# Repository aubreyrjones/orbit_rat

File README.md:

Orbit Rat
---------

[Watch a demo](https://www.youtube.com/watch?v=k3nQiXu3pM4)

THIS IS NOT A MOUSE REPLACEMENT. The Orbit Rat is a Teensy LC based PC input device designed
to facilitate panning and orbiting in CAD and graphic design software.

The concept is similar to the 3dconnexion navigation device. But the Orbit Rat has fewer 
degrees of freedom, much wider compatibility, and much lower cost. The Orbit Rat is not 
quite a space mouse, you see.

The OR is designed around a pair of small joysticks, like those on a gamepad controller. These 
joysticks then control pan and orbit in CAD, art, and graphic design programs by specially
emulating a mouse. _No special drivers or plugins needed_, works in any operating system.

This is not a regular joystick-controlled mouse. OR implements a special "rewind" operation
after every motion, which resets the mouse cursor position and unlocks near-infinite pan/orbit 
in any program that uses middle-click and drag for pan.

The cost to build one is around $30 USD. You could build it without any soldering, using
breadboard, but it will be bulky. You can easily solder it on protoboard with hand wiring.
It's also an easy circuit board to design.

Tested on Linux and Windows. Should work on Mac and mobile OS as well.

Tested to work with default settings in:

* Fusion 360
* Inkscape
* GIMP
* EAGLE CAD

# How it Works

This is pretty configurable, but by default...

When you tilt the stick outside the deadzone, Orbit Rat emulates a mouse holding down the middle
mouse button and starting a drag motion. This starts a pan action in lots of CAD and art software. 
The viewport will move as if you're panning with the mouse so long as you're tiling the stick.

If you think about how your favorite software works, when you finish the pan motion and let go the button,
the mouse is in a different part of the screen than when you started. You have to 
move the cursor back toward the middle of the screen to get more space if you want to continue the pan. 
With a traditional joystick-controlled mouse, this is torture.

But not so with Orbit Rat.

As you move, the OR tracks how much mouse motion it has sent to your computer. When you let
go of the stick, it very quickly moves the cursor back to where it was when you first tilted the stick. 
You can now continue the pan just by tilting the stick again. Or, you can continue your work 
with the cursor just where you left it.

The other stick works very similarly, but also emulates holding down the left shift keyboard button. 
This will activate an orbit in CAD software.

This is almost as much control as a dedicated "3d mouse" with special driver support. The beauty of 
Orbit Rat is that it works everywhere, in any operating system, in any application that uses click 
and drag for pan.

It can also do other stuff, like sending scroll wheel events and keyboard keys... but the rewind
operation is what it does uniquely.

# Features

* User defined list of stick modes and parameters to use. As many as you like until
  you run out of RAM. Most of what's discussed below can be set per mode.

* Cycle through your defined modes by clicking the stick buttons.

* REWIND - stick initiates a mouse movement, then OR returns the cursor to its starting
  position when you let go of the stick.

* STUTTER - similar to rewind mode, but continually moves a set distance, rewinds, then 
  repeats as long as you hold down the button. Not smooth, but allows "infinite" scrolling
  with limited screen real estate.

* SIMPLE - just be a mouse cursor, no rewind.

* SCROLL - stick movement sends scroll wheel commands. Useful for CAD zoom, or
  document scrolling.

* User-defined stick curves, so you can tweak the sensitivity of each stick.

* Invert or ignore any stick axis.

* Choose mouse button(s) and/or keyboard key that is held during mouse motion.

* Auto-calibrates joysticks by default (although not perfectly)

* Configurable to send HID joystick events if desired for custom application code.

* Parts are available circa Q2 2022. Teensy LC available despite chip shortage. 
  Joysticks and other parts available from hobby electronics suppliers (Sparkfun, 
  Adafruit).

# _Planned_ Features

* RGB status LEDs (DotStar) for each stick's modes
* PCB reference design
* Left-handed PCB design

# Limitations

The Orbit Rat is fundamentally impersonating a mouse, so it doesn't have access to any
information a regular dumb mouse wouldn't have. It doesn't get any feedback from the 
operating system.

The main place this shows up is when the cursor hits the edge of the screen during a move.
The Orbit Rat thinks it's still moving the cursor, but the OS doesn't let it leave the screen.
When the OR goes to rewind the cursor motion at the end of the move, it has the wrong
idea of how much to rewind and overshoots.

Additionally, moue wheel scrolling in Linux and Windows is _not_ smooth. It goes in
chunky, discrete increments. Orbit Rat tries its best to send scroll events at a steady
rate, but without special drivers, it can't make the screen animation smooth when
scrolling (like e.g. Apple trackpad scrolling).

# Configuration and Building

Since you need the tools to upload the firmware anyway, I made things easy for me.
Orbit Rat is configured in source code and built with [PlatformIO](https://platformio.org/).

The easiest way to use PlatformIO is just to use VisualStudio Code (not Visual Studio) with
the free PlatformIO plugin from the marketplace. Standalone setups may work but I haven't
tested them.

When you first build, it may seem to stall for a very long time. PlatformIO is downloading a newer
compiler from a very slow connection. It gives no progress indicator. It seriously
took me 20 minutes to download. This only happens the first time you build. It also
may finish the download, try to compile, then say it failed... try again before
concluding it doesn't work.

Configuration is at the top of `main.cpp`. You can learn more about the options in 
`config_types.hpp`.

On your operation system you will need to set the "Teensyduino OrbitRat Mouse" acceleration
to 0. If you don't, the cursor will not return to the correct location. You should be able
to leave acceleration on for your regular mouse however you like it.

## Hardware

This isn't commercial hardware or software. You'll need to cobble together your
own hardware setup.

I'm using a Teensy LC as my microcontroller. I expect Teensy 4.0 would work, but
little is gained from its expanded capabilities. Teensy 3 might work; Teensy 2
is not compatible.

Assuming you'll use the software mostly unmodified, you need to hook up a pair of
potentiometer joysticks to the Teensy's analog inputs. That's pretty much it.

For the prototype I used the model of joystick sold on SparkFun, along with their 
breakout boards. I wired up the axes directly to the Teensy LC analog pins. I added 
pullup resistors on the switches There are internal pullups that could work, but I 
didn't test that way.

You can see my pin assignments in `main.cpp` under `axisPins` and `buttonPins`.
That's also where you can alter them if you'd like to wire the pins up differently.
Note that you _must_ use analog inputs for the joysticks.

## Software

The software isn't written to be especially efficient. It's written for a Teensy LC,
which has a 48MHz core clock. I haven't noticed that input rates are too low, so
I don't worry about a bit of fake floating point.

Calibration is quasi-automatic right now (although you can turn it off). By default, 
the center point is read at startup. Conservative endpoints are taken as a default,
but will expand if they receive a higher value from the hardware during operation. You 
can turn off both these features at the top of `main.cpp`.

## Troubleshooting

> Problem: I flashed the firmware and plugged it into the computer, but my mouse doesn't 
work or moves erratically.

This is "normal" if you flash the Teensy with Orbit Rat firmware, but have not attached
the joysticks to it. Without the joysticks, the Teensy input voltages drift randomly
and result in erratic movement. Ideally, install both joysticks. If you need just
one joystick for some reason, adjust `n_axes` to equal `2` and fix the resultant
compile errors.

## This is not a commercial venture, and the Orbit Rat is not for sale

The whole point of the project is that it's very, very cheap compared to the pro-grade
alternative. Stocking the parts, assembling them, and shipping them takes time
I have no interest in spending. And people have expectations of commercial products
(warranties, returns, etc.) that I don't want to deal with. I have a job, and a
few bucks just isn't worth the hassle.

To make it worth it to me, each unit would need to sell for $100 or more. And
that kind of defeats the purpose.

On the other hand, this is also an absolutely _ideal_ first microcontroller project.
You can build a completely decent version using just breakout- and bread-boards.
It is within your abilities to Orbit Rat. I believe in you.

You can also try one of the circuit boards from the `circuits` directory.
Most of those designs aren't tested, but they're a good starting point for
your design. When I get a design printed and tested, I will mark it 
conspicuously.

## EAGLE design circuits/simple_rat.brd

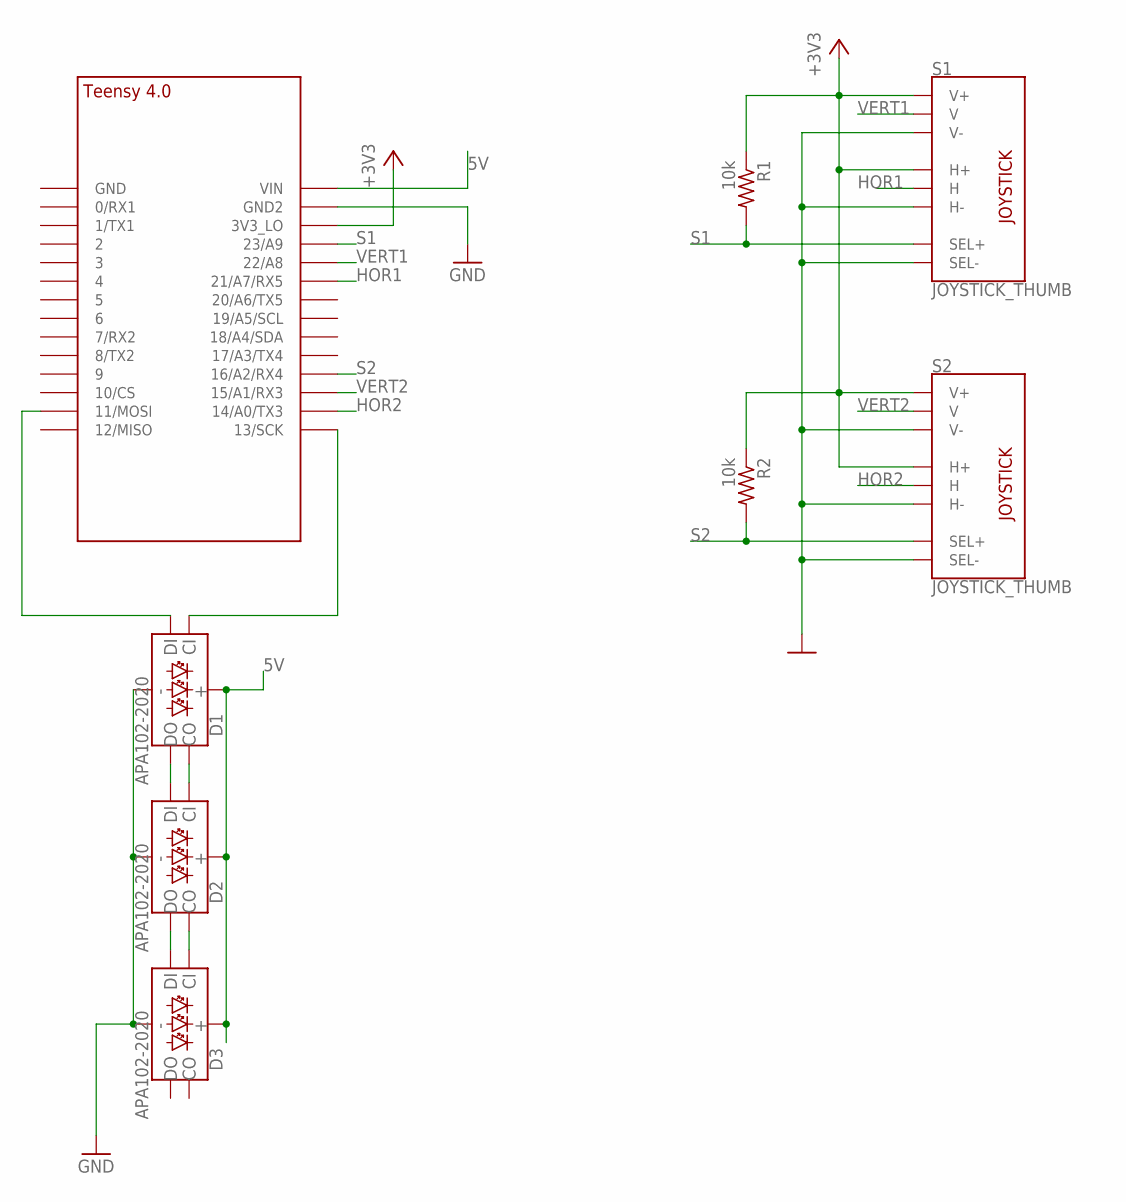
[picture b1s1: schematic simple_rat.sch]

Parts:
D1, D2, D3: APA102-2020
MCU: TEENSY_4.0-NOBOTTOM
R1, R2: 10k; R0603
S1, S2: JOYSTICK_THUMB; JOYSTICK

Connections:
5V: D1.5V_VIA (VCC), D1.VDD (VCC), D2.5V_VIA (VCC), D2.VDD (VCC), D3.5V_VIA (VCC), D3.VDD (VCC), MCU.VIN
+3V3: MCU.3V3_LO, R1.1, R2.1, S1.H1 (H+), S1.V1 (V+), S2.H1 (H+), S2.V1 (V+)
GND: D1.GND, D1.GND_VIA (GND), D2.GND, D2.GND_VIA (GND), D3.GND, D3.GND_VIA (GND), MCU.GND2, S1.B2A (SEL-), S1.H3 (H-), S1.V3 (V-), S2.B2A (SEL-), S2.H3 (H-), S2.V3 (V-)
HOR1: MCU.21/A7 (21/A7/RX5), S1.H2 (H)
HOR2: MCU.14/A0 (14/A0/TX3), S2.H2 (H)
unnamed: D1.SDO (DO), D2.SDI (DI)
unnamed: D1.CKO (CO), D2.CKI (CI)
unnamed: D2.SDO (DO), D3.SDI (DI)
unnamed: D2.CKO (CO), D3.CKI (CI)
unnamed: D1.CKI (CI), MCU.13/SCK
unnamed: D1.SDI (DI), MCU.11/MOSI
S1: MCU.23/A9, R1.2, S1.B1A (SEL+)
S2: MCU.16/A2 (16/A2/RX4), R2.2, S2.B1A (SEL+)
VERT1: MCU.22/A8, S1.V2 (V)
VERT2: MCU.15/A1 (15/A1/RX3), S2.V2 (V)

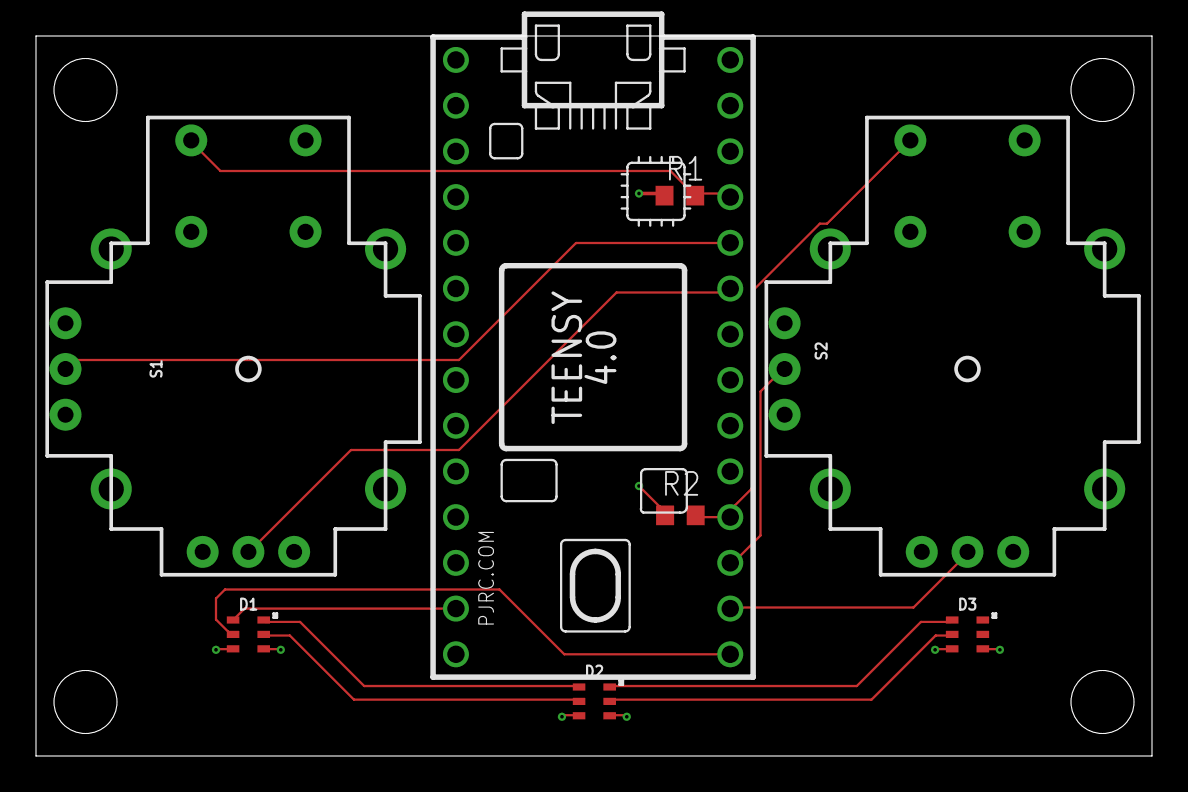
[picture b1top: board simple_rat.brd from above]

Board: 4 copper layers, 62.0 x 40.0 mm, 8 parts (0 on the bottom side), 15 nets.

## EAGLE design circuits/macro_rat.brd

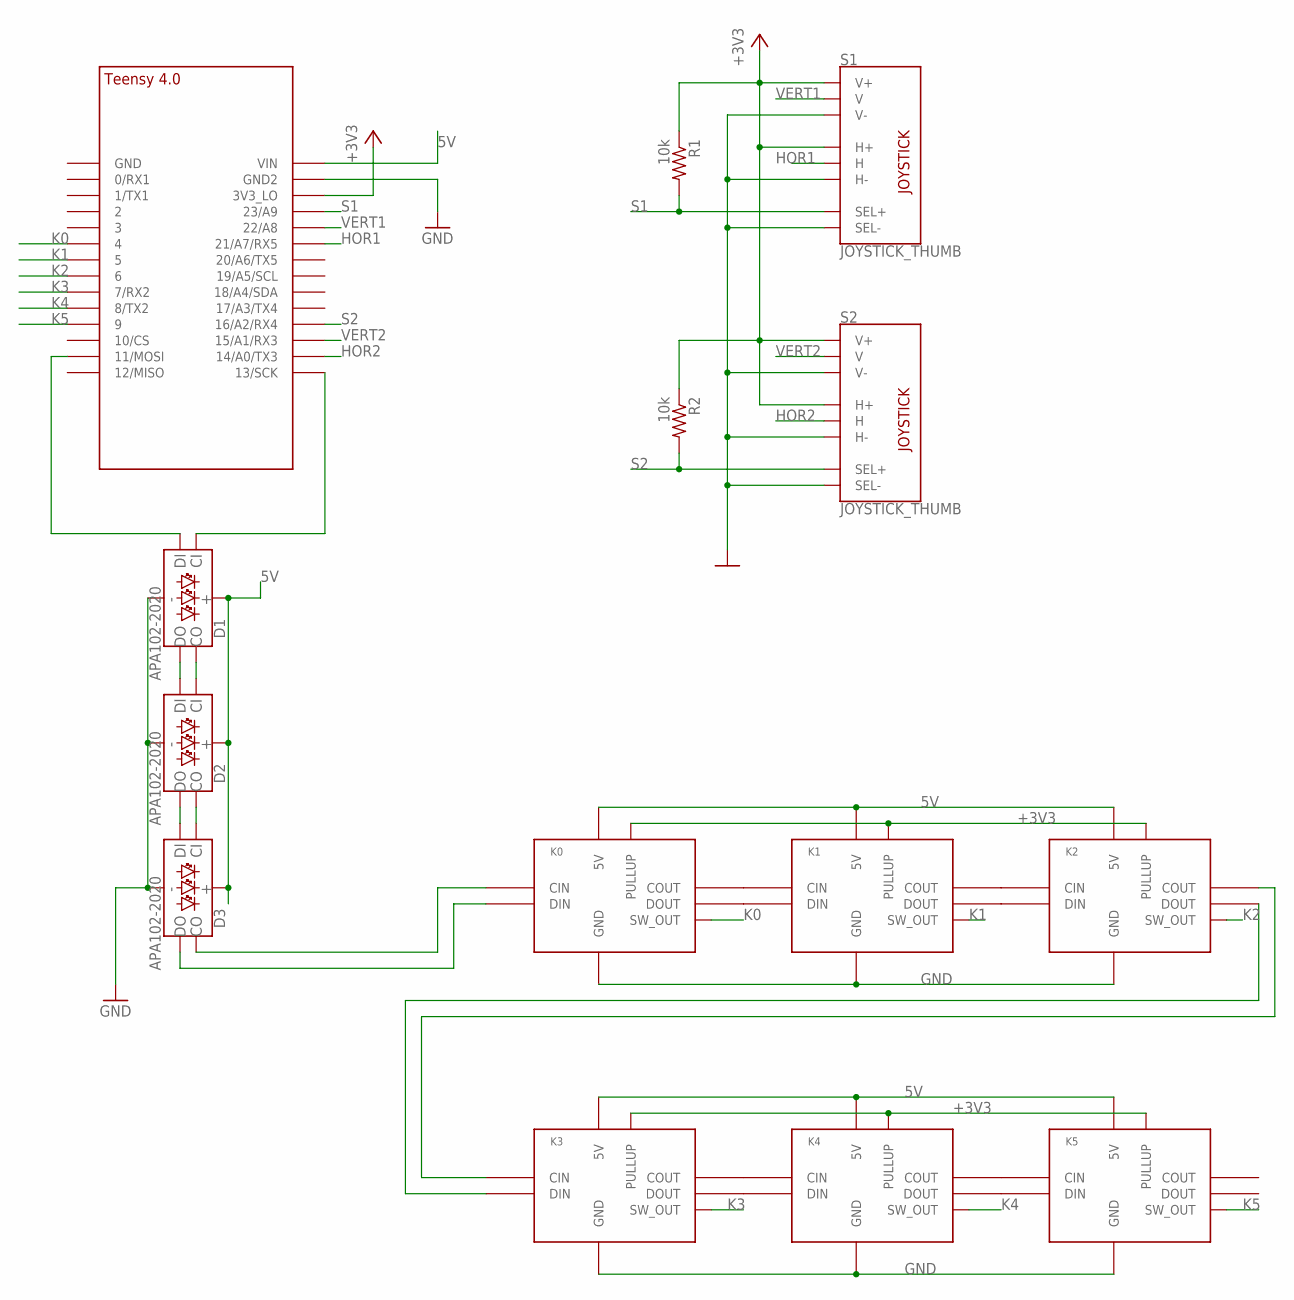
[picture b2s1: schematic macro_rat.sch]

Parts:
D1, D2, D3: APA102-2020
K0, K1, K2, K3, K4, K5: KEY_LED_CHOC_ONESIDERIGHT_HAND; KEY_CHOC_V2_RH
MCU: TEENSY_4.0-NOBOTTOM
R1, R2: 10k; R0603
S1, S2: JOYSTICK_THUMB; JOYSTICK

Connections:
5V: D1.5V_VIA (VCC), D1.VDD (VCC), D2.5V_VIA (VCC), D2.VDD (VCC), D3.5V_VIA (VCC), D3.VDD (VCC), K0.5V, K0.VDD (5V), K1.5V, K1.VDD (5V), K2.5V, K2.VDD (5V), K3.5V, K3.VDD (5V), K4.5V, K4.VDD (5V), K5.5V, K5.VDD (5V), MCU.VIN
+3V3: K0.PULLUP_V (PULLUP), K0.PULLUP_VIA (PULLUP), K1.PULLUP_V (PULLUP), K1.PULLUP_VIA (PULLUP), K2.PULLUP_V (PULLUP), K2.PULLUP_VIA (PULLUP), K3.PULLUP_V (PULLUP), K3.PULLUP_VIA (PULLUP), K4.PULLUP_V (PULLUP), K4.PULLUP_VIA (PULLUP), K5.PULLUP_V (PULLUP), K5.PULLUP_VIA (PULLUP), MCU.3V3_LO, R1.1, R2.1, S1.H1 (H+), S1.V1 (V+), S2.H1 (H+), S2.V1 (V+)
GND: D1.GND, D1.GND_VIA (GND), D2.GND, D2.GND_VIA (GND), D3.GND, D3.GND_VIA (GND), K0.GND, K0.GND$1 (GND), K0.GND$2 (GND), K0.GND$3 (GND), K0.GND$4 (GND), K0.GND_VIA (GND), K1.GND, K1.GND$1 (GND), K1.GND$2 (GND), K1.GND$3 (GND), K1.GND$4 (GND), K1.GND_VIA (GND), K2.GND, K2.GND$1 (GND), K2.GND$2 (GND), K2.GND$3 (GND), K2.GND$4 (GND), K2.GND_VIA (GND), K3.GND, K3.GND$1 (GND), K3.GND$2 (GND), K3.GND$3 (GND), K3.GND$4 (GND), K3.GND_VIA (GND), K4.GND, K4.GND$1 (GND), K4.GND$2 (GND), K4.GND$3 (GND), K4.GND$4 (GND), K4.GND_VIA (GND), K5.GND, K5.GND$1 (GND), K5.GND$2 (GND), K5.GND$3 (GND), K5.GND$4 (GND), K5.GND_VIA (GND), MCU.GND2, S1.B2A (SEL-), S1.H3 (H-), S1.V3 (V-), S2.B2A (SEL-), S2.H3 (H-), S2.V3 (V-)
HOR1: MCU.21/A7 (21/A7/RX5), S1.H2 (H)
HOR2: MCU.14/A0 (14/A0/TX3), S2.H2 (H)
K0: K0.OUT (SW_OUT), K0.OUT_UP (SW_OUT), MCU.4/CANRX (4)
K1: K1.OUT (SW_OUT), K1.OUT_UP (SW_OUT), MCU.5
K2: K2.OUT (SW_OUT), K2.OUT_UP (SW_OUT), MCU.6
K3: K3.OUT (SW_OUT), K3.OUT_UP (SW_OUT), MCU.7 (7/RX2)
K4: K4.OUT (SW_OUT), K4.OUT_UP (SW_OUT), MCU.8 (8/TX2)
K5: K5.OUT (SW_OUT), K5.OUT_UP (SW_OUT), MCU.9/CS (9)
unnamed: K0.CKO (COUT), K1.CKI (CIN)
unnamed: K0.SDO (DOUT), K1.SDI (DIN)
unnamed: K1.CKO (COUT), K2.CKI (CIN)
unnamed: K1.SDO (DOUT), K2.SDI (DIN)
unnamed: K3.CKO (COUT), K4.CKI (CIN)
unnamed: K3.SDO (DOUT), K4.SDI (DIN)
unnamed: K4.CKO (COUT), K5.CKI (CIN)
unnamed: D1.SDO (DO), D2.SDI (DI)
unnamed: D1.CKO (CO), D2.CKI (CI)
unnamed: D2.SDO (DO), D3.SDI (DI)
unnamed: D2.CKO (CO), D3.CKI (CI)
unnamed: D1.CKI (CI), MCU.13/SCK
unnamed: D1.SDI (DI), MCU.11/MOSI
unnamed: K4.SDO (DOUT), K5.SDI (DIN)
unnamed: D3.CKO (CO), K0.CKI (CIN)
unnamed: D3.SDO (DO), K0.SDI (DIN)
unnamed: K2.SDO (DOUT), K3.SDI (DIN)
unnamed: K2.CKO (COUT), K3.CKI (CIN)
S1: MCU.23/A9, R1.2, S1.B1A (SEL+)
S2: MCU.16/A2 (16/A2/RX4), R2.2, S2.B1A (SEL+)
VERT1: MCU.22/A8, S1.V2 (V)
VERT2: MCU.15/A1 (15/A1/RX3), S2.V2 (V)

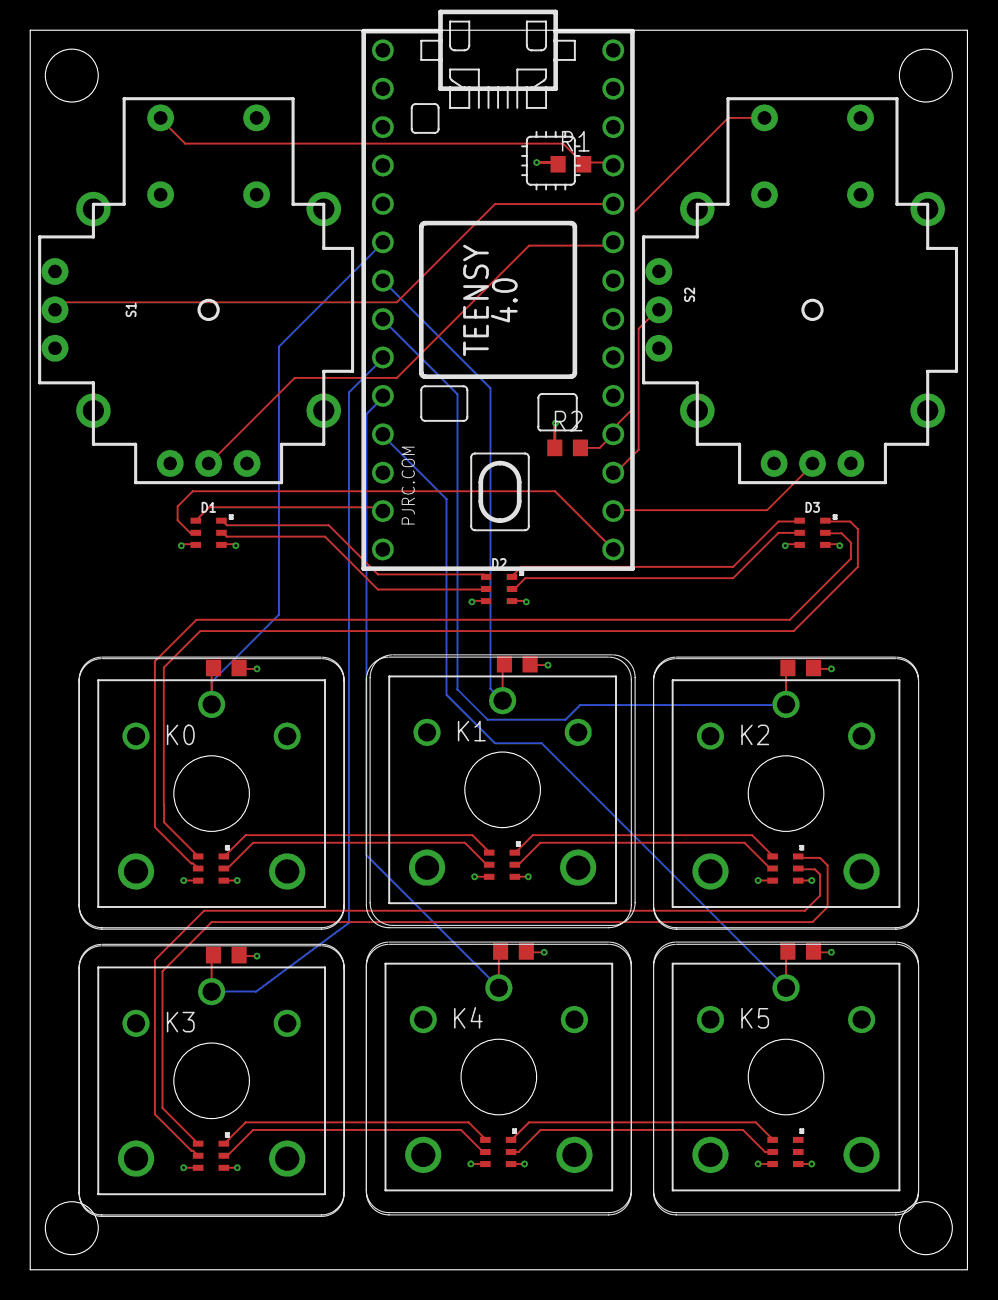
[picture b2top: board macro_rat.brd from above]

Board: 4 copper layers, 62.0 x 82.0 mm, 14 parts (0 on the bottom side), 33 nets.

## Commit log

2022-04-03 Got basic serial output and normalization working.
2022-04-03 Got joysticks working as joysticks.
2022-04-04 mouse unwind works.
2022-04-04 middle click pan works!
2022-04-04 Second curve for the orbit stick.
2022-04-04 Flipped the pan stick inputs.
2022-04-04 Added readme and a little more configuration.
2022-04-04 Made joystick reports optional and improved comments.
2022-04-04 Added image ref.
2022-04-04 Fixed markdown?
2022-04-04 Made unwind step configurable.
2022-04-04 Made it more configurable.
2022-04-04 Updated docs.
2022-04-05 Updated readme.
2022-04-05 Finished a rev a, but it's enormous.
2022-04-06 Gonna rewrite a bit.
2022-04-06 Buttons reporting now.
2022-04-06 Configurability and STUTTER mode.
2022-04-06 Gottta do some interpolation, hope the float doesn't kill me.
2022-04-06 Added comments, changed USB device name, improved scrolling.
2022-04-06 Trying to add expo, but want better compiler for constexpr.
2022-04-06 Upgraded to gcc 9.3 for that good constexpr, included arm math library.
2022-04-06 Muahahah..
2022-04-06 Have linear expo working.
2022-04-06 Improved scrolling behavior and curve.
2022-04-07 USB diving.
2022-04-07 Fiddling with how curves work, trading memory for quality in scrolling.
2022-04-07 Trying again on the circuit, fiddling with settings for nice scrolling in eagle.
2022-04-07 Switched the expo tables from floats to shorts for a bit of performance and memory savings.
2022-04-07 code organization.
2022-04-07 More docs!
2022-04-07 Docs, configs, and playing with build options.
2022-04-07 docs update.
2022-04-10 Updated docs, also sent `rev_d` to production.
2022-04-13 typo
2022-04-13 diagnostics output on a predicate
2022-04-13 flash LED on setup
2022-04-13 add mode switch led flash
2022-04-13 Working through feature suggestions.
2022-04-13 Improved readability, configuration.
2022-04-13 Can i embed video in markup?
2022-04-13 Nope.
2022-04-14 Added Caleb's demo.
2022-04-17 Working on raw hid endpoint for feedback from system.
2022-04-17 Working on basic xlib stuff to get focused window and screen edges.
2022-04-22 Circuit boards are supposed to show up today.
2022-04-24 Lots of progress in hardware and software.
2022-04-24 Added builtin LED status/processing monitor.
2023-02-12 I don't remember, honestly. It's been a year since I worked on this.
2023-02-12 Added debug support for macro keys.
2023-02-12 Much hacking, but got LEDs working.
2023-04-05 Lots of support for macro keys and RGBs.

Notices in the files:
parts and their libraries:
SparkFun-Switches: Licensing: Creative Commons ShareAlike 4.0 International - https://creativecommons.org/licenses/by-sa/4.0
